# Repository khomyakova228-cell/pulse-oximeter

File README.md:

<div class="title-page" align="center">

<table class="title-head"><tr>
<td></td>
<td align="center">
<b>Министерство науки и высшего образования Российской Федерации</b><br>
<b>Федеральное государственное автономное образовательное учреждение высшего образования</b><br>
<b>«Московский государственный технический университет имени Н.Э. Баумана<br>
(национальный исследовательский университет)»</b><br>
<b>(МГТУ им. Н.Э. Баумана)</b>
</td></tr></table>

<p class="tp-line">ФАКУЛЬТЕТ <u>БИОМЕДИЦИНСКАЯ ТЕХНИКА</u></p>
<p class="tp-line">КАФЕДРА <u>МЕДИКО-ТЕХНИЧЕСКИЕ ИНФОРМАЦИОННЫЕ ТЕХНОЛОГИИ (БМТ-2)</u></p>

<p class="tp-title">Домашнее задание</p>
<p class="tp-sub">по курсу «САПР электронных средств»</p>
<p class="tp-topic">«Проект печатного узла пульсоксиметра в KiCad:<br>оформление по ГОСТ, библиотека компонентов, автоматизация проверки и выпуска»</p>
<p class="tp-sub">Обозначение документа: БИГЕ.149980.001 Э3</p>

<table class="tp-sign">
<tr><td>Группа</td><td><u>БМТ2-31М</u></td><td></td></tr>
<tr><td>Студент</td><td>_________________</td><td><u>Хомякова А.А.</u></td></tr>
<tr><td></td><td class="hint">подпись, дата</td><td class="hint">фамилия, и.о.</td></tr>
<tr><td>Преподаватель</td><td>_________________</td><td><u>Рязанцев П.</u></td></tr>
<tr><td></td><td class="hint">подпись, дата</td><td class="hint">фамилия, и.о.</td></tr>
</table>

<p class="tp-city">Москва, 2026 г.</p>
</div>

<div class="page-break"></div>

## Содержание

- [Задание](#задание)
- [1. Библиотека компонентов (УГО + посадочные места)](#1-библиотека-компонентов-уго--посадочные-места)
- [2. Схема электрическая принципиальная](#2-схема-электрическая-принципиальная)
- [3. Файл печатной платы](#3-файл-печатной-платы)
- [4. Скрипт проверки и выпуска (bash / bat)](#4-скрипт-проверки-и-выпуска-bash--bat)
- [5. Git-репозиторий и GitHub](#5-git-репозиторий-и-github)
- [Заключение: выполнение пунктов задания](#заключение-выполнение-пунктов-задания)

## Задание

Общее задание: создать проект печатной платы в KiCad. Проект должен содержать:

1. **Библиотеку компонентов** (УГО + посадочные места). УГО компонентов оформить по ГОСТ.
   Библиотека должна подключаться к проекту как git-сабмодуль. Пути библиотек должны быть
   относительными.
2. **Схему электрическую принципиальную**, оформленную по ГОСТ (как минимум рамка и основная
   надпись). Все «важные» цепи (шины питания, основные сигнальные цепи) описаны в классах цепей
   (допустимо цветовое обозначение). В полях компонентов завести `Manufacturer_Part_Number` с
   реальным партномером компонента.
3. **Файл печатной платы.** При трассировке учитывать технологические возможности завода «Резонит»,
   соблюдать технологичность платы (DFMA-подход).
4. **Скрипт bash** (для Windows — файл `.bat`): проверка ERC, DRC, генерация Gerber-файлов,
   BOM (перечень элементов), PDF-версии схемы.

Проект размещается в git-репозитории на персональной странице GitHub. Отчёт — PDF-версия файла
`README.md` (этот документ). Разделы 1–4 отчёта соответствуют пунктам задания 1–4, раздел 5 —
требованию о git-репозитории и GitHub.

Объект проектирования — **пульсоксиметр**: двухканальный оптический датчик (два светодиода и
фотодиод), аналоговый тракт на ОУ, микроконтроллер STM32F030 и преобразователь USB–UART.
Работа выполнена в KiCad 10.0.

## 1. Библиотека компонентов (УГО + посадочные места)

### 1.1. Состав библиотеки

Библиотека — отдельный git-репозиторий `kicad-gost-lib`, подключённый к проекту сабмодулем.

```
kicad-gost-lib/
├── symbols/GOST_UGO.kicad_sym          УГО компонентов по ГОСТ (21 шт.)
├── footprints/GOST_FP.pretty/          посадочные места (19 шт.)
├── drawing_sheets/GOST_form1.kicad_wks рамка листа и основная надпись, ГОСТ 2.104, форма 1
├── tools/gen_gost_lib.py               генератор УГО (символы описаны кодом)
├── tools/gen_wks.py                    генератор рамки
└── docs/                               изображения
```

### 1.2. УГО по ГОСТ

Все компоненты схемы проверены на соответствие таблицам ГОСТ 2.721, 2.728, 2.730, 2.743, 2.755, 2.759
(таблица 1). Штатные символы KiCad выполнены по ANSI/IEC; там, где форма отличается от ЕСКД, нарисованы
собственные УГО, и вся схема переведена на библиотеку GOST_UGO (рисунок 1, таблица 2).

<p class="caption tcap">Таблица 1 — Проверка УГО схемы на соответствие ГОСТ</p>

| Компоненты | Было (KiCad) | Соответствие ГОСТ | Что сделано |
|---|---|---|---|
| DA1–DA7 (ОУ) | `Amplifier_Operational` — треугольник | нет: ГОСТ 2.759 требует прямоугольник с «▷∞» | `GOST_UGO:OPA340P` |
| DA8, DA9, DD1, DD2 | прямоугольник без полей | нет: ГОСТ 2.743 — основное и дополнительные поля | `KR590KN2`, `LM1117MP-ADJ`, `STM32F030C8Tx`, `FT232RL` |
| X1 | `Conn_01x03` — колодка | нет: ГОСТ 2.755 — табличная форма | `Conn_1x03` |
| SW1–SW3 | `SW_Omron_B3FS` | нет: ГОСТ 2.755 — замыкающий контакт 30°, нажимной привод | `SW_Push_NO` |
| GND (36 шт.) | `power:GND` — треугольник | нет: ГОСТ 2.721 табл. 6б п. 4 — «⊥» | `GND` |
| R13, R19, R20, R29, R37, R44 | `R_Potentiometer` — стрелка (переменный) | нет: подстроечный по ГОСТ 2.728 — отрезок с «Т» | `R_Trim` |
| C1–C49 | `Device:C`, зазор между пластинами = 3/8 длины | нет: ГОСТ 2.728 — пластины 8 мм, зазор 1,5 мм | `C` |
| HL1, HL2 | `Device:LED`, корпус Ø5,7, треугольник 53° | частично: ГОСТ 2.730 — корпус Ø10 (1:2 → Ø5), 60° | `LED` |
| VD1 | `BPW34` | частично: ГОСТ 2.730 — фотодиод в корпусе, стрелки внутрь 45° | `Photodiode` |
| VT1, VT2 | `BD235`, угол К–Э 90° | нет: ГОСТ 2.730 — корпус Ø12, угол К–Э 60° | `Q_NPN` |
| VD2–VD5 | `ZYxxx` | да по форме (черта с одним отгибом), треугольник 53° | `D_Zener` (60°) |
| R (34 шт.) | `Device:R` 5,08 × 2,03 | да (10 × 4 в масштабе 1:2) | `R` — для единообразия библиотеки |
| Шины питания «Б», «В», «А» (31 шт.) | `power:+12V`, `power:+3.3V` | форма допустима (стрелка с наименованием цепи), но символ из штатной библиотеки | `PWR` — та же форма, имя цепи = значение |
| PWR_FLAG (3 шт.) | `power:PWR_FLAG` | служебный символ ERC, на печать не выводится | `PWR_FLAG` |

Дискретные элементы выполнены в масштабе 1:2 к размерам из таблиц ГОСТ: так они ложатся на сетку
KiCad 2,54 мм, и все УГО на листе уменьшены одинаково. Выводы новых символов стоят в тех же точках и
с теми же номерами, что у штатных, поэтому символы заменены без изменения проводов. После замены
проверено, что список связей схемы (`kicad-cli sch export netlist`) не изменился. В итоговой схеме
все 93 компонента и все символы питания взяты из библиотеки `GOST_UGO` — штатных символов KiCad не
осталось.

Символы описаны кодом
(`tools/gen_gost_lib.py`), поэтому размеры, шаг выводов и шрифты задаются в одном месте и
одинаковы во всех символах.

<p class="caption">Рисунок 1 — УГО библиотеки GOST_UGO</p>

<p class="caption tcap">Таблица 2 — УГО библиотеки</p>

| Символ | Поз. обозн. | Стандарт | Особенности |
|---|---|---|---|
| `OPA340P` | DA | ГОСТ 2.759, 2.743 | основное поле со знаком «▷∞», инвертирующий вход — указатель инверсии, питание отдельной группой |
| `KR590KN2` | DA | ГОСТ 2.743 | функция «SW», группы: управление D1–D4, входы, выходы, питание |
| `LM1117MP-ADJ` | DA | ГОСТ 2.743 | вход и ADJ слева, выход справа |
| `STM32F030C8Tx` | DD | ГОСТ 2.743 | функция «MCU», выводы сгруппированы по портам, питание отдельной группой |
| `FT232RL` | DD | ГОСТ 2.743 | функция «USB/UART», выводы с активным низким уровнем — кружком |
| `Conn_1x02…1x06` | X | ГОСТ 2.755 | таблица «Конт. / Цепь», наименования цепей — поля экземпляра `Цепь1…ЦепьN` |
| `SW_Push_NO` | SB | ГОСТ 2.755, 2.721 | замыкающий контакт, нажимной привод, механическая связь |
| `GND` | — | ГОСТ 2.721 | «электрическое соединение с корпусом (общий провод)», «⊥» |
| `PWR` | — | ГОСТ 2.702 | шина питания: стрелка с наименованием цепи («Б», «В», «А»); имя цепи — значение символа |
| `PWR_FLAG` | — | — | служебный флаг источника питания для ERC, в документ не выводится |
| `R`, `R_Trim` | R | ГОСТ 2.728 | 10 × 4 (1:2); подстроечный — отрезок с «Т» |
| `C` | C | ГОСТ 2.728 | пластины 8, зазор 1,5 (1:2) |
| `LED`, `Photodiode` | HL, VD | ГОСТ 2.730 | корпус Ø10 (1:2), треугольник 60°, стрелки 45° наружу / внутрь |
| `D_Zener` | VD | ГОСТ 2.730 | черта катода с одним отгибом |
| `Q_NPN` | VT | ГОСТ 2.730 | корпус Ø12 (1:2), угол коллектор–эмиттер 60°, стрелка эмиттера |

Общие правила: у ИМС основное и дополнительные поля, группы выводов разделены линией и пустым шагом,
корпус без заливки, толщина линий УГО равна толщине линий связи, шаг выводов 2,54 мм. В каждом
символе заполнены поля `Footprint` (ссылка на `GOST_FP`), `Datasheet`, `Manufacturer`,
`Manufacturer_Part_Number`.

### 1.3. Посадочные места

Все посадочные места проекта (19 шт.) перенесены в библиотеку `GOST_FP.pretty` (таблица 3). Основа —
официальная библиотека KiCad (IPC-7351). Посадочные места хранятся вместе с проектом, поэтому плата
не меняется при обновлении библиотек, установленных вместе с KiCad. В схеме и на плате все
компоненты ссылаются на `GOST_FP:…`.

<p class="caption tcap">Таблица 3 — Посадочные места библиотеки GOST_FP</p>

| Посадочное место | Компоненты |
|---|---|
| `R_Axial_DIN0309_L9.0mm_D3.2mm_P2.54mm_Vertical` | резисторы R1–R63 |
| `Potentiometer_Bourns_3296W_Vertical` | подстроечные R13, R19, R20, R29, R37, R44 |
| `C_Disc_D5.1mm_W3.2mm_P5.00mm` | конденсаторы C1–C49 |
| `DIP-8_W7.62mm`, `DIP-16_W7.62mm` | DA1–DA7 (OPA340), DA8 (КР590КН2) |
| `LQFP-48_7x7mm_P0.5mm`, `SSOP-28_5.3x10.2mm_P0.65mm` | DD1 (STM32), DD2 (FT232RL) |
| `TO-220-3_Vertical` (и запасной `SOT-223-3_TabPin2`) | DA9 (LM1117T-ADJ) |
| `TO-126-3_Vertical` | VT1, VT2 |
| `D_DO-41_SOD81_P10.16mm_Horizontal` | стабилитроны VD2–VD5 |
| `Osram_DIL2_4.3x4.65mm_P5.08mm` | фотодиод VD1 (BPW34) |
| `LaserDiode_TO18-D5.6-3` | светодиоды HL1, HL2 |
| `SW_PUSH_6mm` | кнопки SW1–SW3 |
| `PinHeader_1x02…1x06_P2.54mm_Vertical` | соединитель X1 (и запасные варианты) |

### 1.4. Подключение библиотеки как git-сабмодуля

```bash
cd pulse-oximeter
git submodule add ../kicad-gost-lib.git lib/kicad-gost-lib
git commit -m "Библиотека kicad-gost-lib подключена сабмодулем"
```

Файл `.gitmodules`:

```
[submodule "lib/kicad-gost-lib"]
    path = lib/kicad-gost-lib
    url = ../kicad-gost-lib.git
```

Адрес сабмодуля **относительный**: он отсчитывается от адреса основного репозитория. Если оба
репозитория лежат в одном аккаунте GitHub, адрес сам превращается в
`https://github.com/<логин>/kicad-gost-lib.git`, и при переносе или форке ничего менять не нужно.
Проект зафиксирован на конкретной версии (коммите) библиотеки. Обновить библиотеку:

```bash
git submodule update --remote lib/kicad-gost-lib
git commit -am "Обновлена библиотека kicad-gost-lib"
```

### 1.5. Относительные пути

Все пути к библиотекам и рамке заданы через `${KIPRJMOD}` — папку проекта. Абсолютных путей в
файлах проекта нет.

`sym-lib-table`:

```
(lib (name "GOST_UGO")(type "KiCad")
     (uri "${KIPRJMOD}/lib/kicad-gost-lib/symbols/GOST_UGO.kicad_sym")(options "")(descr "УГО по ЕСКД"))
```

`fp-lib-table`:

```
(lib (name "GOST_FP")(type "KiCad")
     (uri "${KIPRJMOD}/lib/kicad-gost-lib/footprints/GOST_FP.pretty")(options "")(descr "Посадочные места"))
```

Рамка (схема и плата): `${KIPRJMOD}/lib/kicad-gost-lib/drawing_sheets/GOST_form1.kicad_wks`.
3D-модели — из штатной библиотеки KiCad через переменную `${KICAD10_3DMODEL_DIR}`.

## 2. Схема электрическая принципиальная

### 2.1. Схема и функциональные узлы

Схема приведена на рисунке 2, функциональные узлы — в таблице 4.

<p class="caption tcap">Таблица 4 — Функциональные узлы схемы</p>

| Узел | Элементы | Назначение |
|---|---|---|
| Ввод питания | X1 | ±12 В и общий провод (цепи «Б», «В», GND) |
| Стабилизатор | DA9 (LM1117-ADJ), R62, R63, C49 | питание цифровой части (цепь «А») |
| Источники опорного напряжения | VD2–VD5, R14, R25, R31, R42, R15, R26, R34, R43, R19, R29, R37, R44 | четыре регулируемых опорных уровня |
| Коммутатор | DA8 (КР590КН2) | выбор опорного уровня сигналами МК (цепи `SW_D1`…`SW_D4`) |
| Стабилизаторы тока светодиодов | DA1, VT1, R8 — HL1; DA5, VT2, R23 — HL2 | ток излучателей задаётся опорным напряжением |
| Фотоприёмник | VD1 (BPW34), DA2 | преобразование тока фотодиода в напряжение |
| Фильтрация и усиление | DA3, DA4, DA6, DA7 с RC-цепями | выделение пульсовой составляющей, усиление до уровня АЦП |
| Микроконтроллер | DD1 (STM32F030C8T6), SW1–SW3, C21–C25 | АЦП, управление коммутатором, кнопки, сброс |
| Интерфейс USB–UART | DD2 (FT232RL) | связь с компьютером (UART МК — PA9/PA10) |

<div class="landscape">

<p class="caption">Рисунок 2 — Схема электрическая принципиальная БИГЕ.149980.001 Э3 (лист A3, цвет линий — класс цепи)</p>

</div>

### 2.2. Оформление по ГОСТ: рамка и основная надпись

Рамка `GOST_form1.kicad_wks` из библиотеки (генератор `tools/gen_wks.py`): поле подшивки 20 мм,
остальные поля 5 мм, основная надпись по **форме 1** ГОСТ 2.104 (185 × 55 мм), дополнительные
графы 19–26, надписи «Копировал» и «Формат». Графы заполняются в *Файл → Параметры страницы*
(таблица 5). Значения хранятся в файлах схемы и платы, формат листа подставляется автоматически
(`${PAPER}`). Схема выполнена на листе **A3**, чертёж платы — на листе **A4**.

<p class="caption tcap">Таблица 5 — Заполнение основной надписи</p>

| Графа ГОСТ 2.104 | Поле KiCad | Схема | Плата |
|---|---|---|---|
| 2, 26 — обозначение документа | Comment 1 | БИГЕ.149980.001 Э3 | БИГЕ.149980.001 |
| 1 — наименование изделия | Title | Пульсоксиметр | Пульсоксиметр |
| 1 — наименование документа | Comment 2 | Схема электрическая принципиальная | Плата печатная |
| Разраб. | Comment 3 | Хомякова А.А. | Хомякова А.А. |
| Пров. | Comment 4 | Рязанцев П. | Рязанцев П. |
| Т.контр., Н.контр., Утв. | Comment 5–7 | — | — |
| 9 — организация | Company, Comment 8, 9 | МГТУ им. Н.Э. Баумана, Кафедра БМТ-2, Группа БМТ2-31М | то же |
| Лист / Листов, Формат | `${#}`, `${##}`, `${PAPER}` | 1 / 1, A3 | 1 / 1, A4 |

<p class="caption">Рисунок 3 — Основная надпись схемы (форма 1 ГОСТ 2.104)</p>

### 2.3. Классы цепей

Классы заданы в *Файл → Параметры схемы → Проект → Классы цепей* и хранятся в
`pulse_oximeter.kicad_pro` (таблица 6). Цепи назначаются классам по **шаблонам имён** (раздел
*Назначения классов цепей* в том же окне), поэтому классы автоматически применяются и к новым цепям.
Цвет класса — цвет линий связи на схеме (рисунок 2), ширина — ширина проводника, которую
трассировщик платы подставляет по умолчанию.

<p class="caption tcap">Таблица 6 — Классы цепей</p>

| Класс | Цепи (шаблоны имён) | Цвет на схеме | Проводник, мм |
|---|---|---|---|
| Power_12V | шины питания `Б` (+12 В), `В` (−12 В) | бирюзовый | 0,5 |
| Power_3V3 | шина питания `А` (выход DA9) | красный | 0,4 |
| GND | `GND` (общий провод) | синий | 0,5 |
| Analog | основные сигнальные цепи аналогового тракта: `*PD_*`, `*TIA*`, `*LPF*`, `*NOTCH*`, `*HPF*`, `*ADC*`, `*REF*`, `*LED*`; прочие цепи тракта `Net-(DA*`, `Net-(VD*`, `Net-(HL*`, `Net-(VT*`, `Net-(R*`, `Net-(C*` | жёлтый | 0,25 |
| Digital | `*SW_D*` (управление коммутатором), `*UART*`, `*NRST*`, `*BTN*`, `Net-(DD*` | фиолетовый | 0,25 |
| Default | прочие | — | 0,2 |

Шины питания и общий провод обозначены символами `PWR` и `GND` из библиотеки, имя цепи — значение
символа (`Б`, `В`, `А`, `GND`). Основные сигнальные цепи обозначены **метками** (*Разместить → Метка*,
клавиша **L**) — таблица 7. Имя локальной метки KiCad хранит с префиксом листа (`/TIA_OUT`), поэтому
шаблоны записаны со звёздочкой: `*TIA*` совпадает и с `TIA_OUT`, и с `/TIA_OUT`. Сигнальные цепи,
которые в исходной схеме были оформлены символами питания (`Г`, `В2`, `В10`, `В12`, `В13`), переведены
на метки: символ питания годится только для шин питания.

<p class="caption tcap">Таблица 7 — Метки основных цепей</p>

| Метка | Где стоит | Что за цепь | Класс |
|---|---|---|---|
| `PD_K` | VD1, вывод 1 (катод) | фотодиод → инвертирующий вход DA2 | Analog |
| `PD_A` | VD1, вывод 2 (анод) | смещение фотодиода (R11, R12, R13) | Analog |
| `TIA_OUT` | DA2, вывод 6 | выход трансимпедансного усилителя | Analog |
| `LPF_OUT` | DA3, вывод 6 | выход ФНЧ | Analog |
| `NOTCH_OUT` | DA4, вывод 6 | выход режекторного фильтра (двойной Т-мост C3, C4, R6, R7) | Analog |
| `HPF_OUT` | DA6, вывод 6 | выход ФВЧ | Analog |
| `ADC_IN` | DA7, вывод 6 и DD1, вывод 11 (PA1) | сигнал на АЦП МК | Analog |
| `REF1`…`REF4` | DA8, выводы 2, 5, 11, 14 (IN1…IN4) | опорные напряжения со стабилитронов | Analog |
| `LED1_REF`, `LED2_REF` | DA8, выводы 1, 6 (OUT1, OUT2) | задание тока светодиодов HL1, HL2 | Analog |
| `SW_D1`…`SW_D4` | DA8, выводы 3, 4, 12, 13 и DD1, выводы 20, 21, 25, 26 | управление коммутатором | Digital |
| `UART_TX`, `UART_RX` | DD1, выводы 30 (PA9), 31 (PA10) | UART МК ↔ DD2 | Digital |
| `NRST` | DD1, вывод 7 | сброс, кнопка SW1 | Digital |
| `BTN1`, `BTN2` | DD1, выводы 18 (PB0), 22 (PB11) | кнопки SW2, SW3 | Digital |

По списку цепей (`kicad-cli sch export netlist`) проверено, что каждая цепь схемы попадает в класс:
Analog — 35, Digital — 9, Power_12V — 2, Power_3V3 — 1, GND — 1. В класс Default попадают только
74 одиночных неиспользуемых вывода, отмеченных флагом «не подключено» (`unconnected-…`).

### 2.4. Поле Manufacturer_Part_Number

У всех компонентов заполнены поля `Manufacturer` и `Manufacturer_Part_Number`. Поля
редактировались в *Инструменты → Массовое редактирование полей символов* с группировкой по номиналу
и посадочному месту: партномер вписывается один раз на группу одинаковых компонентов. Партномера
сверены по каталогам поставщиков (LCSC, RS, Element14, Future Electronics). Перечень элементов
(таблица 8) формирует скрипт (раздел 4).

<p class="caption tcap">Таблица 8 — Перечень элементов (output/pulse_oximeter_BOM.csv)</p>

| Поз. обозначение | Номинал / тип | Кол. | Производитель | Manufacturer_Part_Number |
|---|---|---|---|---|
| C1–C27, C33, C49 | 100 нФ, X7R, 50 В | 29 | Murata | RDER71H104K0P1H03B |
| DA1–DA7 | OPA340P | 7 | Texas Instruments | OPA340PA |
| DA8 | КР590КН2 | 1 | — | КР590КН2 |
| DA9 | LM1117T-ADJ (TO-220) | 1 | Texas Instruments | LM1117T-ADJ/NOPB |
| DD1 | STM32F030C8T6 | 1 | STMicroelectronics | STM32F030C8T6 |
| DD2 | FT232RL | 1 | FTDI | FT232RL-REEL |
| HL1, HL2 | светодиод | 2 | Vishay | TSAL6200 |
| R1, R4–R7, R11, R12, R18, R21, R23, R28, R62 | 10 кОм, 0,5 Вт, 1 % | 12 | YAGEO | MFR50SFTE52-10K |
| R2, R3, R9, R10, R16, R17, R22, R35, R40 | 22 кОм, 0,5 Вт, 1 % | 9 | YAGEO | MFR50SFTE52-22K |
| R8, R14, R24, R25, R27, R30, R31, R42, R63 | 390 Ом, 0,5 Вт, 1 % | 9 | YAGEO | MFR50SFTE52-390R |
| R13, R19, R20, R29, R37, R44 | 10 кОм, подстроечный | 6 | Bourns | 3296W-1-103LF |
| R15, R26, R34, R43 | 2,2 кОм, 0,5 Вт, 1 % | 4 | YAGEO | MFR50SFTE52-2K2 |
| SW1–SW3 | кнопка 6 × 6 мм | 3 | Omron | B3F-1000 |
| VD1 | фотодиод | 1 | Vishay | BPW34 |
| VD2–VD5 | стабилитрон 5,1 В | 4 | Vishay | 1N4733A |
| VT1, VT2 | n-p-n транзистор | 2 | STMicroelectronics | BD139-16 |
| X1 | вилка 1 × 3, 2,54 мм | 1 | Würth Elektronik | 61300311121 |

## 3. Файл печатной платы

### 3.1. Конструкция

<p class="caption tcap">Таблица 9 — Параметры платы</p>

| Параметр | Значение |
|---|---|
| Размер | 78 × 79,5 мм, 4 крепёжных отверстия по углам |
| Слои | 2 (F.Cu, B.Cu), FR-4 1,6 мм, медь 35 мкм |
| Компоненты | 93 шт., все на верхней стороне; 256 выводных и 76 SMD-площадок (DD1, DD2) |
| Проводники | 0,254 мм — сигнальные, 0,4 мм — питание, 0,2 мм — 12 коротких участков |
| Переходные отверстия | 3 шт., площадка 1,7 мм, отверстие 1,0 мм |
| Полигоны | GND на обоих слоях |

### 3.2. Технологические возможности «Резонит»

Использованы значения класса **«Стандарт» (4 класс точности)** для одно- и двусторонних плат с медью
35 мкм. Источник — таблица технологических возможностей на сайте завода:
<https://www.rezonit.ru/pcb/odnostoronnie-i-dvustoronnie/serial/>. Значения заданы в настройках
платы (*Файл → Параметры платы → Ограничения*) и продублированы правилами в файле
`pulse_oximeter.kicad_dru`, поэтому DRC (и скрипт из раздела 4) проверяет плату именно по ним
(таблица 10).

<p class="caption tcap">Таблица 10 — Ограничения «Резонит» и их выполнение</p>

| Параметр | «Резонит», «Стандарт» | Правило DRC | На плате |
|---|---|---|---|
| Ширина проводника (медь 35 мкм) | ≥ 0,20 мм | 0,20 мм | 0,20 / 0,254 / 0,4 мм |
| Зазор медь — медь | ≥ 0,20 мм | 0,20 мм | ≥ 0,20 мм (DRC: 0 ошибок) |
| Металлизированное отверстие | ≥ 0,30 мм | 0,30 мм | ≥ 0,6 мм |
| Поясок контактной площадки | ≥ 0,20 мм | 0,20 мм | выполнено (DRC) |
| Поясок переходного отверстия | ≥ 0,15 мм | 0,15 мм | 0,35 мм |
| Неметаллизированное отверстие | ≥ 0,50 мм | 0,50 мм | нет |
| Перемычка паяльной маски (зелёная) | ≥ 0,10 мм | проверка `solder_mask_bridge` | нарушений нет |
| Маркировка: линия / высота | ≥ 0,15 / 1,0 мм | 0,15 / 1,0 мм | выполнено (DRC) |
| Медь до края платы | ≥ 0,25 мм (фрезеровка), ≥ 0,40 мм (скрайбирование) | 0,40 мм | ≥ 0,40 мм (DRC) |

### 3.3. Технологичность (DFMA)

* **Односторонний монтаж.** Все компоненты на верхней стороне: плата собирается за один проход,
  без переворота и второй операции пайки.
* **Преимущественно выводной монтаж**, SMD только у DD1 (LQFP-48, шаг 0,5 мм) и DD2 (SSOP-28,
  шаг 0,65 мм). Эти шаги укладываются в возможности завода и ручного монтажа.
* **Запас по технологическим нормам.** Сигнальные проводники 0,254 мм и проводники питания 0,4 мм
  при минимуме 0,2 мм; переходные отверстия 1,0 мм при минимуме 0,3 мм. Плату можно изготовить по
  самому дешёвому классу точности.
* **Минимум переходных отверстий** (3 шт.): основная трассировка на верхнем слое, нижний слой — под
  перемычки и полигон GND.
* **Сплошные полигоны GND** на обоих слоях снижают помехи в аналоговом тракте и уменьшают объём
  травления меди.
* **Медь не ближе 0,4 мм к краю**, 4 крепёжных отверстия по углам, маркировка не мельче 1 мм —
  проверяется DRC по правилам из `pulse_oximeter.kicad_dru`.
* **Стандартные номиналы и корпуса**: все компоненты из распространённых серий с реальными
  партномерами (таблица 8), без заказных элементов. Стабилизатор DA9 — в выводном корпусе TO-220
  (LM1117T-ADJ), как и остальная выводная часть платы.
* **Маркировка.** Позиционные обозначения нанесены на слой F.Silkscreen высотой 1 мм. DRC выдаёт
  15 предупреждений о наложении надписей маркировки друг на друга (например, R17/R18, DA7/R20) —
  на изготовление они не влияют, но перед заказом надписи стоит раздвинуть (клавиша **M** на тексте).

### 3.4. Изображения платы

<p class="caption">Рисунок 4 — Плата, 3D-вид сверху</p>

<p class="caption">Рисунок 5 — Плата, 3D-вид снизу</p>

<p class="caption">Рисунок 6 — Слои меди: F.Cu (слева) и B.Cu, вид снизу (справа)</p>

<div class="landscape">

<p class="caption">Рисунок 7 — Плата на листе A4 с рамкой и основной надписью по ГОСТ 2.104</p>

</div>

## 4. Скрипт проверки и выпуска (bash / bat)

### 4.1. Шаги скрипта

Скрипт проверки и выпуска выполнен в двух вариантах: `scripts/build.bat` (Windows) и
`scripts/build.sh` (bash). Оба выполняют одинаковые шаги через консольную утилиту KiCad `kicad-cli`
(таблица 11).

<p class="caption tcap">Таблица 11 — Шаги скрипта</p>

| Шаг | Команда `kicad-cli` | Результат |
|---|---|---|
| 1. ERC | `sch erc --severity-all` | `output/reports/erc.rpt` |
| 2. DRC + сверка со схемой | `pcb drc --schematic-parity --severity-all` (правила «Резонит») | `output/reports/drc.rpt` |
| 3. Gerber | `pcb export gerbers` (F/B.Cu, Mask, Paste, Silkscreen, Edge.Cuts) | `output/gerber/*.g*` |
| 3. Сверловка | `pcb export drill --excellon-separate-th --generate-map` | `output/gerber/*.drl`, карты сверловки |
| 3. Архив для завода | `Compress-Archive` / `zip` | `output/pulse_oximeter_gerber.zip` |
| 4. BOM | `sch export bom` (группировка по номиналу, корпусу, партномеру) | `output/pulse_oximeter_BOM.csv` |
| 5. PDF схемы | `sch export pdf` (цветная и `--black-and-white`) | `output/pulse_oximeter_schematic*.pdf` |
| 6. 3D-модель | `pcb export step` | `output/pulse_oximeter.step` |

Запуск:

```bat
scripts\build.bat                              :: Windows (или двойной щелчок по файлу)
```

```bash
./scripts/build.sh                             # Linux / macOS / Git Bash
KICAD_CLI=/путь/к/kicad-cli ./scripts/build.sh
```

Вывод скрипта:

```
=== 1/6 ERC — проверка электрических правил схемы ===
Found 0 violations
  ошибок: 0, предупреждений: 0  ->  output/reports/erc.rpt
=== 2/6 DRC — проверка правил проектирования платы ===
Found 51 violations
Found 0 unconnected items
Found 3 schematic parity issues
  ошибок: 0, предупреждений: 54  ->  output/reports/drc.rpt
=== 3/6 Gerber и файлы сверловки ===
Plotted to 'output/gerber/pulse_oximeter-F_Cu.gtl'.   … (9 слоёв)
Created file 'output/gerber/pulse_oximeter-PTH.drl'
=== 4/6 BOM — перечень элементов ===
Wrote bill of materials to 'output/pulse_oximeter_BOM.csv'.
=== 5/6 PDF схемы ===
Plotted to 'output/pulse_oximeter_schematic.pdf'.
=== 6/6 3D-модель платы (STEP) ===
  output/pulse_oximeter.step
=== Итог ===
  ERC и DRC без ошибок, файлы выпущены.
```

### 4.2. Результаты проверки

<p class="caption tcap">Таблица 12 — Результат прогона скрипта</p>

| Проверка | Ошибок | Предупреждений | Что означает |
|---|---|---|---|
| ERC | 0 | 0 | схема полностью разведена: неиспользуемые выводы отмечены флагами «не подключено» (50 шт.), шины `Б`, `В`, `GND` от разъёма X1 отмечены `PWR_FLAG` |
| DRC | 0 | 54 | нарушений правил «Резонит» нет, все соединения разведены (0 неразведённых) |

**Предупреждения DRC** (на изготовление не влияют):

* 35 — `lib_footprint_mismatch`: у резисторов и разъёма X1 на плате посадочные места из библиотеки
  KiCad 10, а в `GOST_FP` — из KiCad 9 (отличаются служебными полями, геометрия площадок та же).
  Устраняется командой *Инструменты → Обновить посадочные места из библиотеки*;
* 15 — `silk_overlap` и 1 — `silk_over_copper`: наложение надписей маркировки (раздел 3.3);
* 3 — `net_conflict`: у одной и той же цепи (C16 — R28 — R30 — DA6, вывод 2) на плате и в схеме
  разные автоматические имена (`Net-(DA6-Pad2)` и `Net-(C16-Pad2)`), соединения при этом
  одинаковые. Устраняется командой *Обновить плату из схемы* (F8).

## 5. Git-репозиторий и GitHub

### 5.1. Состав репозитория проекта

```
pulse-oximeter/
├── pulse_oximeter.kicad_pro     проект: классы цепей, ограничения «Резонит», рамка, настройки BOM
├── pulse_oximeter.kicad_sch     схема электрическая принципиальная (A3)
├── pulse_oximeter.kicad_pcb     печатная плата
├── pulse_oximeter.kicad_dru     правила DRC «Резонит»
├── sym-lib-table, fp-lib-table  таблицы библиотек (пути через ${KIPRJMOD})
├── lib/kicad-gost-lib/          ← git-сабмодуль: УГО, посадочные места, рамка
├── scripts/build.sh, build.bat  проверка и выпуск
├── docs/                        изображения для отчёта
├── README.md, README.pdf        отчёт
├── .gitmodules, .gitignore, .gitattributes
└── output/                      результаты скрипта (создаётся при запуске, в git не хранится)
```

`.gitignore` исключает из репозитория резервные копии KiCad (`*-backups/`, `_autosave-*`, `*.lck`),
кэш (`fp-info-cache`), личные настройки (`*.kicad_prl`) и папку `output/`. `.gitattributes` задаёт
окончания строк: LF для `.sh` и файлов KiCad, CRLF для `.bat`.

## Заключение: выполнение пунктов задания

<p class="caption tcap">Таблица 13 — Выполнение пунктов задания</p>

| Пункт задания | Где выполнено | Результат |
|---|---|---|
| 1. Библиотека УГО + посадочные места | `lib/kicad-gost-lib`: `GOST_UGO.kicad_sym`, `GOST_FP.pretty` | 21 УГО по ГОСТ 2.702/2.721/2.728/2.730/2.743/2.755/2.759, все символы схемы — из GOST_UGO; 19 посадочных мест, все компоненты платы — из GOST_FP |
| 1. Подключение git-сабмодулем | `.gitmodules`, `lib/kicad-gost-lib` | относительный адрес `../kicad-gost-lib.git` |
| 1. Относительные пути | `sym-lib-table`, `fp-lib-table`, рамка | везде `${KIPRJMOD}` |
| 2. Схема по ГОСТ | `pulse_oximeter.kicad_sch`, рамка `GOST_form1` | лист A3, рамка и основная надпись по форме 1 ГОСТ 2.104 |
| 2. Классы цепей | `pulse_oximeter.kicad_pro`, метки на схеме | 5 классов с цветами; все цепи схемы распределены по классам |
| 2. Manufacturer_Part_Number | поля компонентов, BOM | заполнено у всех компонентов (таблица 8) |
| 3. Плата, «Резонит», DFMA | `pulse_oximeter.kicad_pcb`, `.kicad_dru` | DRC по нормам «Резонит»: 0 ошибок, 0 неразведённых соединений |
| 4. Скрипт bash / bat | `scripts/build.sh`, `scripts/build.bat` | ERC (0 ошибок), DRC (0 ошибок), Gerber + сверловка, BOM, PDF схемы, STEP |
| Git и GitHub | репозитории `pulse-oximeter`, `kicad-gost-lib` | проект и библиотека в git, библиотека подключена сабмодулем |
| Отчёт | `README.md`, `README.pdf` | этот документ |

Все пункты задания выполнены: библиотека УГО и посадочных мест по ГОСТ подключена к проекту
git-сабмодулем с относительными путями; схема оформлена по ГОСТ, важные цепи описаны в классах
цепей, у всех компонентов заполнен `Manufacturer_Part_Number`; плата разведена с учётом
технологических возможностей завода «Резонит» и проходит DRC без ошибок; скрипты `build.bat` и
`build.sh` выполняют ERC, DRC, выпуск Gerber-файлов, BOM и PDF схемы; проект размещён в
git-репозитории, отчёт — PDF-версия файла `README.md`.

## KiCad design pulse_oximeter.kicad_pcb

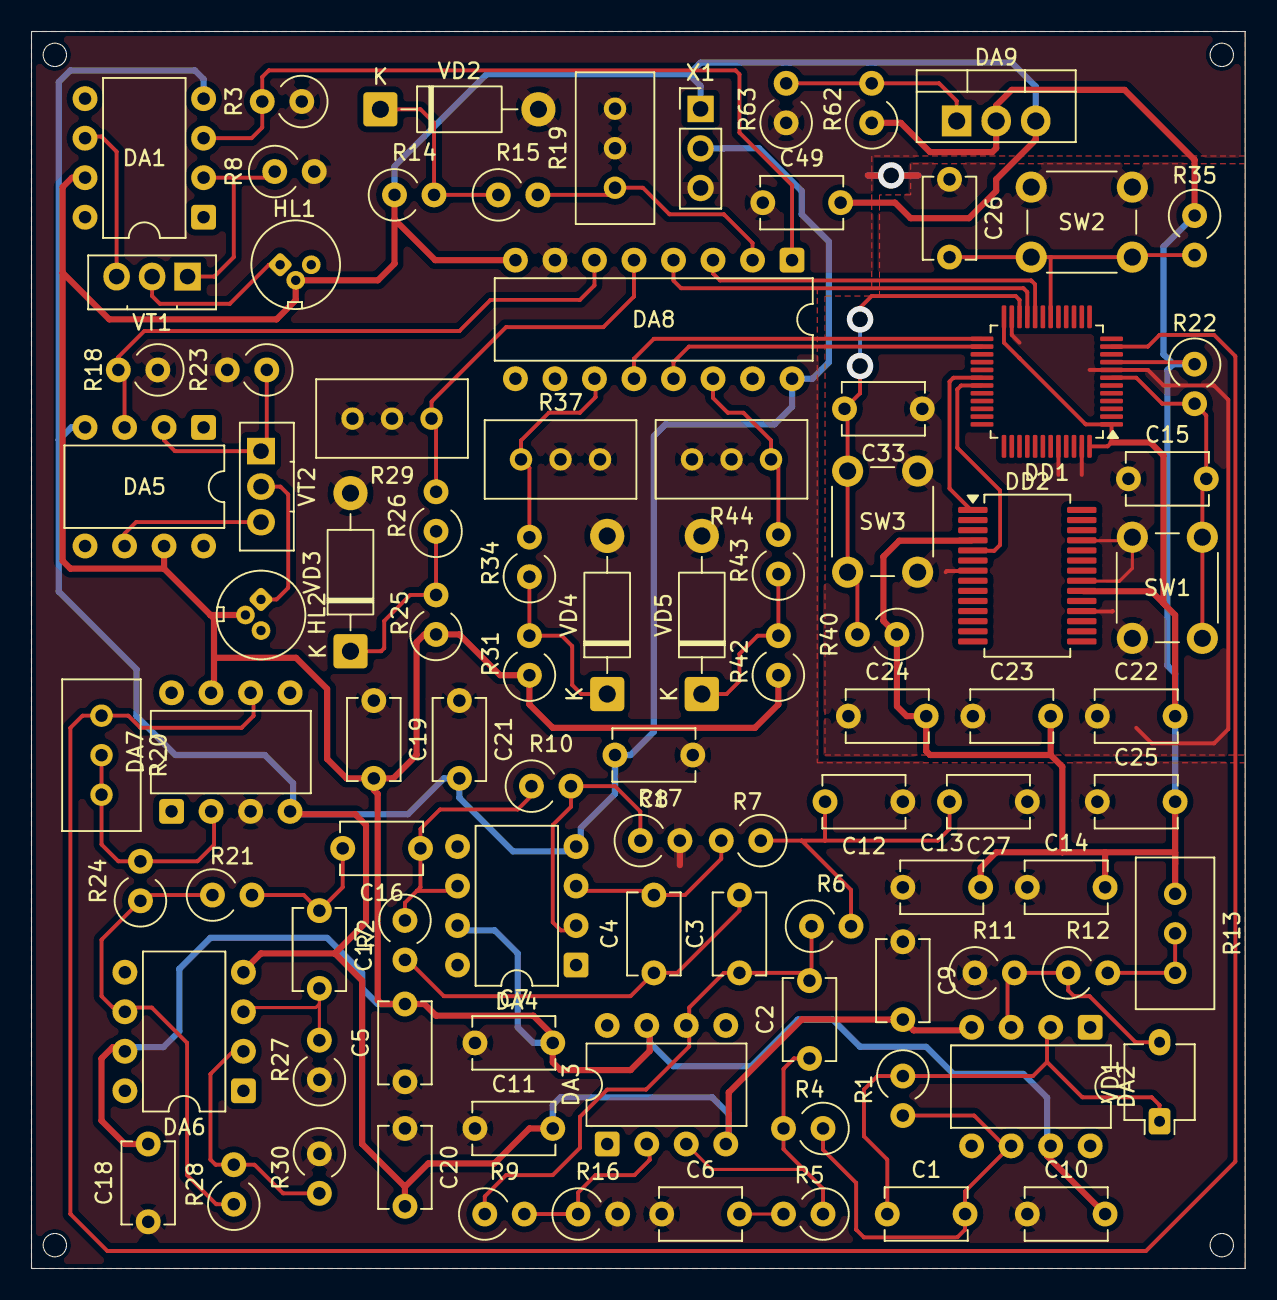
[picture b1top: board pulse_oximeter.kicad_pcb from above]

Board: 2 copper layers, 78.0 x 79.5 mm, 93 parts (0 on the bottom side), 49 nets.

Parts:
C1, C2, C3, C4, C5, C6, C7, C8, C9, C10, C11, C12, C13, C14, C15, C16, C17, C18, C19, C20, C21, C22, C23, C24, C25, C26, C27, C33, C49: 100n; C_Disc_D5.1mm_W3.2mm_P5.00mm
DA1, DA2, DA3, DA4, DA5, DA6, DA7: OPA340P; DIP-8_W7.62mm
DA8: КР590КН2; DIP-16_W7.62mm
DA9: LM1117T-ADJ; TO-220-3_Vertical
DD1: STM32F030C8T6; LQFP-48_7x7mm_P0.5mm
DD2: FT232RL; SSOP-28_5.3x10.2mm_P0.65mm
HL1, HL2: TSAL6200; LaserDiode_TO18-D5.6-3
R1, R4, R5, R6, R7, R11, R12, R18, R21, R23, R28, R62: 10k; R_Axial_DIN0309_L9.0mm_D3.2mm_P2.54mm_Vertical
R2, R3, R9, R10, R16, R17, R22, R35, R40: 22k; R_Axial_DIN0309_L9.0mm_D3.2mm_P2.54mm_Vertical
R8, R14, R24, R25, R27, R30, R31, R42, R63: 390; R_Axial_DIN0309_L9.0mm_D3.2mm_P2.54mm_Vertical
R13, R19, R20, R29, R37, R44: 10k; Potentiometer_Bourns_3296W_Vertical
R15, R26, R34, R43: 2.2k; R_Axial_DIN0309_L9.0mm_D3.2mm_P2.54mm_Vertical
SW1, SW2, SW3: B3F-1000; SW_PUSH_6mm
VD1: BPW34; Osram_DIL2_4.3x4.65mm_P5.08mm
VD2, VD3, VD4, VD5: 5V1; D_DO-41_SOD81_P10.16mm_Horizontal
VT1, VT2: BD139-16; TO-126-3_Vertical
X1: Conn_01x03; PinHeader_1x03_P2.54mm_Vertical

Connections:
/ADC_IN: DA7.6, DD1.11 (PA1), R20.3
/BTN1: C26.2, DD1.18 (PB0), R35.2, SW2.2
/BTN2: C33.2, DD1.22 (PB11), R40.2, SW3.2
/HPF_OUT: DA6.6, R21.1, R24.1, R28.1
/LED1_REF: DA1.3, DA8.1 (OUT1), R3.2
/LED2_REF: DA5.3, DA8.6 (OUT2), R18.2
/LPF_OUT: C2.2, C3.1, DA3.6, R6.1, R9.1
/NOTCH_OUT: C16.1, DA4.6, R2.1, R10.1
/NRST: C15.2, DD1.7 (RST), R22.2, SW1.2
/PD_A: DA2.3, R11.2, R12.1, VD1.2 (A)
/PD_K: C1.1, DA2.2, R1.1, VD1.1 (K)
/REF1: DA8.2 (IN1), R15.2, R19.3
/REF2: DA8.5 (IN2), R26.2, R29.3
/REF3: DA8.11 (IN3), R34.2, R37.3
/REF4: DA8.14 (IN4), R43.2, R44.3
/SW_D1: DA8.3 (D1), DD1.20 (PB2)
/SW_D2: DA8.4 (D2), DD1.21 (PB10)
/SW_D3: DA8.12 (D3), DD1.25 (PB12)
/SW_D4: DA8.13 (D4), DD1.26 (PB13)
/TIA_OUT: C1.2, DA2.6, R1.2, R4.1
/UART_RX: DD1.31 (PA10), DD2.5 (RXD)
/UART_TX: DD1.30 (PA9), DD2.1 (TXD)
GND: C5.1, C6.1, C7.1, C8.1, C9.1, C10.1, C11.1, C12.1, C13.1, C14.1, C15.1, C18.1, C19.1, C20.1, C21.1, C22.1, C23.1, C24.1, C25.1, C26.1, C27.1, C33.1, C49.1, DA7.3, DA8.7 (0V), DD1.8 (VSSA), DD1.23 (VSS), DD1.44 (BOOT0), DD1.47 (VSS), DD2.7 (GND), DD2.18 (GND), DD2.21 (GND), DD2.25 (AGND), R3.1, R8.2, R11.1, R16.2, R17.2, R18.1, R19.1, R19.2, R23.2, R27.1, R29.1, R29.2, R30.1, R37.1, R37.2, R44.1, R44.2, R63.1, SW1.1, SW2.1, SW3.1, VD2.2 (A), VD3.2 (A), VD4.2 (A), VD5.2 (A), X1.3
unnamed: C2.1, DA3.3, R4.2, R5.1
unnamed: C3.2, C4.1, R2.2
unnamed: C4.2, DA4.3, R7.2
unnamed: C6.2, R5.2
unnamed: C12.2, C27.2, R6.2, R7.1
unnamed: C16.2, C17.1, R21.2
unnamed: C17.2, DA6.3, R27.2
unnamed: DA3.2, R9.2, R16.1
unnamed: DA4.2, R10.2, R17.1
unnamed: DA6.2, R28.2, R30.2
unnamed: DA7.2, R20.1, R20.2, R24.2
unnamed: DA9.1 (ADJ), R62.2, R63.2
unnamed: HL1.1 (K), VT1.2 (C)
unnamed: HL2.1 (K), VT2.2 (C)
unnamed: R12.2, R13.1, R13.2
unnamed: R14.2, R15.1, VD2.1 (K)
unnamed: R25.2, R26.1, VD3.1 (K)
unnamed: R31.2, R34.1, VD4.1 (K)
unnamed: R42.2, R43.1, VD5.1 (K)
unnamed: DA1.6, VT1.3 (B)
unnamed: DA1.2, R8.1, VT1.1 (E)
unnamed: DA5.6, VT2.3 (B)
unnamed: DA5.2, R23.1, VT2.1 (E)
А: C13.2, C14.2, C22.2, C23.2, C24.2, C25.2, DA9.2 (OUT), DD1.1 (VDD), DD1.9 (VDDA), DD1.24 (VDD), DD1.48 (VDD), DD2.4 (VCCIO), DD2.20 (VCC), R13.3, R22.1, R35.1, R40.1, R62.1
Б: C5.2, C7.2, C10.2, C18.2, C19.2, C49.2, DA1.7 (+U), DA2.7 (+U), DA3.7 (+U), DA4.7 (+U), DA5.7 (+U), DA6.7 (+U), DA7.7 (+U), DA8.8 (+U), DA9.3 (IN), HL1.2 (A), HL2.2 (A), R14.1, R25.1, R31.1, R42.1, X1.1
В: C8.2, C9.2, C11.2, C20.2, C21.2, DA1.4 (-U), DA2.4 (-U), DA3.4 (-U), DA4.4 (-U), DA5.4 (-U), DA6.4 (-U), DA7.4 (-U), DA8.16 (-U), X1.2
